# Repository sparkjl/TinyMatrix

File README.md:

## TinyMatrix点阵控制器
> 基于STM32F103 Microcontroller，HUB75接口的点阵控制器。可通过1 x 4按键、串口指令控制LED点阵屏显示。

### 1. 硬件
#### 1.1. HUB75接口定义
Led点阵板的HUB75接口，一般以DC3-16P牛角座封装形式接入。通常Led点阵板的左右两侧各有一个HUB75接口IN、OUT，以实现多块Led点阵板的组合扩展。HUB75接口中：R1、G1、B1分别为上半屏的红、绿、蓝控制信号，R2、G2、B2分别为下半屏的红、绿、蓝控制信号，A、B、C、D、E为行选择信号，CLK为数据时钟信号，LAT为数据锁存信号，OE为输出使能信号，GND为信号地。

<div align="center">
    
</div>

#### 1.2. HUB75扫描方式
将行扫描信号、行选择信号进行组合控制，就实现了整个Led点阵板的扫描显示。其具体实现过程如下：

<div align="center">
    
</div>

1. 从DATA_IN引脚（R1、G1、B1、R2、G2、B2）写入1 bit数据，将CLK引脚拉高产生上升沿将数据写入移位寄存器。如此循环m次将一行m bit数据传输至移位寄存器。
2. 将LATCH、<SPAN style="TEXT-DECORATION: overline">OE</SPAN>引脚拉高，m bit数据被从移位寄存器传输至缓存寄存器。同时缓存寄存器中数据被保持禁止从输出驱动器中输出，以使得在行选择信号切换时没有Led被点亮。
3. 切换并输出行选择信号。(初始状态时，第0行、第32行被选中。)
4. 将LATCH、<SPAN style="TEXT-DECORATION: overline">OE</SPAN>引脚拉低，m bit数据被从缓存寄存器传输至输出驱动器。同时移位寄存器中数据被锁存禁止从缓存寄存器中移出，此时对应选中行Led被点亮。

将以上步骤执行n/2次，便能实现m x n像素Led点阵板整个画面的扫描显示。如果扫描频率足够低，我们能看到逐行扫描显示的全过程：

<div align="center">
    
</div>

基于人眼视觉暂留效应（余晖效应），我们无法分辨刷新率在24Hz以上的动态画面。如果将扫描频率设置在60Hz，我们就能看到一幅完整的静态画面。而这也就是常见的显示器的基本原理。

最后，将Led点阵板上下两个部分的R1、G1、B1、R2、G2、B2控制信号进行组合，便能基于光学RGB模型实现全彩显示。

#### 1.3. Led Matrix控制板设计
了解了HUB75接口的控制原理，接下来进行Led Matrix控制板设计。

Led Matrix控制板设计思路如下：

<div align="center">
    
</div>

Led Matrix控制板的核心选择的是一款尺寸为 22.86mm x 53.34mm 的STM32最小系统板。其通过2 x 20Pin GPIO排针将板载STM32F103C8T6 MCU内集成的2x SPI、3x USART、2x I2C、1x CAN、37x I/O、2x ADC、4x Timer等硬件资源引出，以便外围扩展板调用。固件程序可通过SWD接口进行烧录和调试，可通过Reset键复位。板载2路Led灯，一路用于电源状态指示，一路用于程序状态指示。

<div align="center">
    
</div>

Led Matrix控制板设计1 x 4按键用于点阵控制器的参数设置。MCU相关GPIO经由74HC245连接至HUB75接口，以增加驱动电流并将驱动电压从3.3v转换至5.0v。外挂的W25Qxx系列SPI Flash用于存储系统参数和字库数据。UART串口可用于下载系统参数和字库数据，TTL-蓝牙模块、TTL-WiFi模块通过UART串口建立与MCU间的通讯以实现控制指令、显示数据的无线透传。Led Matrix控制板由外接电源适配器或内置锂离子电池提供系统电源，直流降压电路实现系统电源从12v-> 5v-> 3.3v电压转换以给各功能单元供电。

基于以上硬件需求，将Led Matrix控制板通过Eagle PCB设计如下。至于为什么是Eagle PCB，那是因为其小巧精悍、简单易用，丰富的元件库、精美的原理图、标准vector字体，无不透露着严谨精致。可惜的是，被Autodesk收购后的Eagle 9.6.2对于3D模型的预览编辑需要通过Fusion 360来实现。

<div align="center">
    
</div>
<div align="center">
    
</div>

### 2. 结构

Eagle 9.6.2不支持直接编辑3D封装，而只能通过Fusion 360以云托管元件库的方式导入。不想从Fusion 360中重构元件库，但又追求项目完整性，这怎么解决呢？那就选择KiCad，不仅支持3D封装的直接编辑，还能将Eagle的.sch原理图文件、.brd电路板文件转换成对应的KiCad格式文件。

使用KiCad将Led Matrix控制板的Eagle格式文件转换成KiCad格式文件，基于此添加编辑3D封装，导出Led Matrix控制板3D Step模型文件。

使用KiCad对MCU核心板重新进行layout，添加编辑3D封装，导出MCU核心板3D Step模型文件。

在Fusion 360中将Led Matrix控制板和MCU核心板进行零件装配、干涉检查。

在Fusion 360中将Led Matrix控制板设置为固定零件，以此为基准依据Led Matrix控制板的空间尺寸设计Led Matrix控制器的整体结构。选择亚克力板材作为外壳材质。顶部和底部亚克力板通过双通螺母柱进行连接，Led Matrix控制板和Led点阵板与底部亚克力板连接固定，四侧亚克力板与顶部和底部亚克力板通过卡扣扣合进行连接。

### 3. 软件
#### 3.1. RGB LED全彩显示
控制RGB LED实现全彩显示的传统方式是脉宽调制（Pulse Width Modulation），简称PWM。通过脉宽调制控制LED开关时间占比，进而实现RGB LED的亮度调节。如果对RGB模块中的三个LED进行此操作，则可以将红绿蓝三色按比例混合成对应的RGB全彩输出。对于Led Matrix Panel的全彩显示，PWM方式却不适用：这需要足够多的GPIO和定时器独立控制，需要消耗太多的硬件资源。那么我们如何通过软件方式予以解决呢？  

二进制编码调制（Binary Code Modulation），简称BCM。BCM利用二进制编码性质控制开关信号占空比。假设有一个位宽为4的二进制数：从其最低位向左移动至最高位依次表示1个时间切片、2个时间切片、4个时间切片、8个时间切片。将这4种时间切片混合，可产生分辨率为1/15的任意占空比。如此，位宽越大分辨率越高色彩越丰富。位宽为8的二进制数，可表示分辨率为1/255的任意占空比。但位宽越大，时间切片越小，意味着更高的CPU占用率。为更好地平衡系统性能和硬件资源，本项目中BCM位宽为4。例如，4位二进制数0101表示5/15或33.3%的占空比。

<div align="center">
    
</div>

Led Matrix Panel是逐行扫描显示的，所以需要预先将图像像素色彩转换成BCM值保存至图像缓冲区。创建4个图像缓冲区，以表示BCM位宽为4情况下的4种长度的时间切片中在扫描时间范围内哪些时间切片需要点亮LED。将这4个图像缓冲区构成的4个颜色通道Plane，进行图像融合就构成了一幅完整的静态图像。

<div align="center">
    
</div>

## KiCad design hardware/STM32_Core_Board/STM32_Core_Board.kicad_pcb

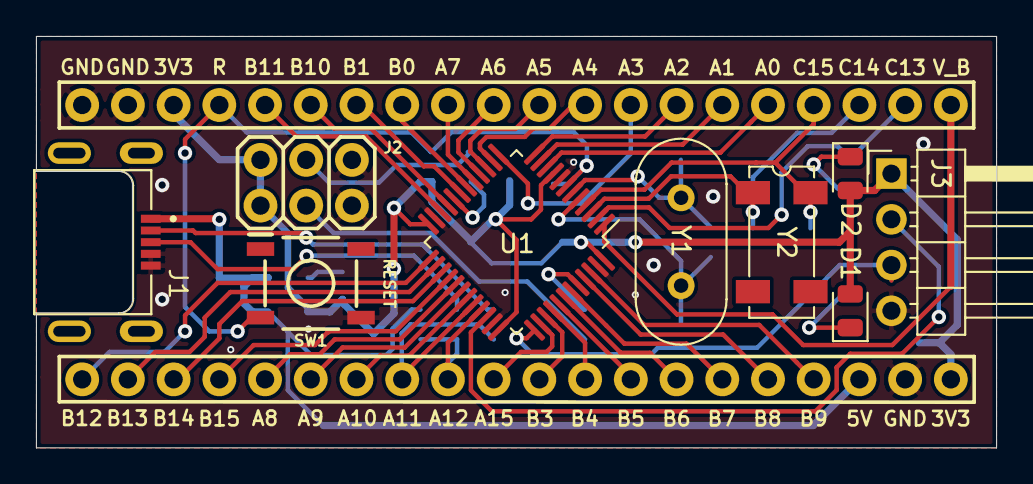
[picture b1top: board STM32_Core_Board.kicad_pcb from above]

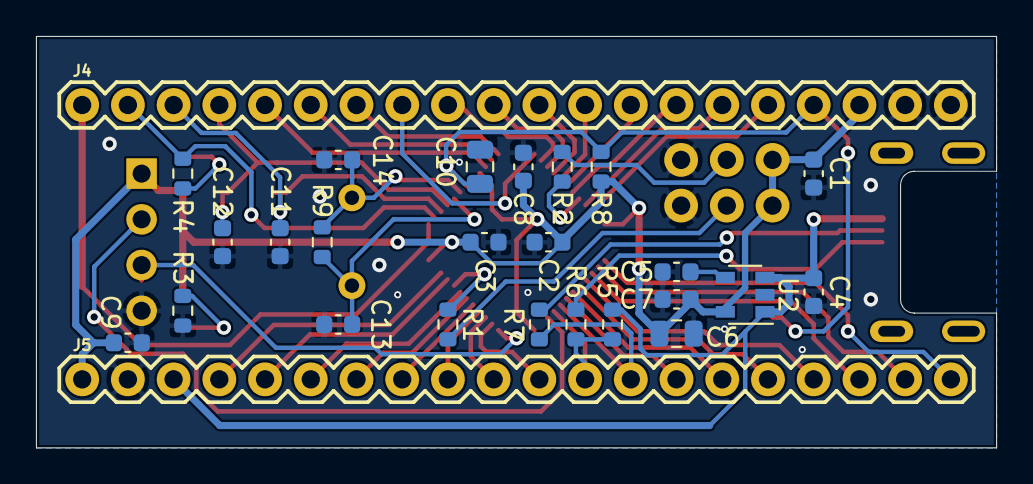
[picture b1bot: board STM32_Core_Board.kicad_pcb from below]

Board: 2 copper layers, 53.3 x 22.9 mm, 35 parts (26 on the bottom side), 50 nets.

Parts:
C1, C2, C3, C7, C8, C9: 104; C_0603_1608Metric
C4: 105; C_0603_1608Metric
C5: 223; C_0603_1608Metric
C6: 106; C_0805_2012Metric
C10: 105; C_0805_2012Metric
C11, C12, C13, C14: 20pF; C_0603_1608Metric
D1, D2: LED; LED_0805_2012Metric
J1: USB_B_Micro; USB_Micro-B-MOLEX_47642-0001
J2: Header 3x2; 2X3
J3: SWD; PinHeader_1x04_P2.54mm_Horizontal
J4, J5: Conn_01x20_Male; 1X20
R1, R2: 100K; R_0603_1608Metric
R3, R4: 510R; R_0603_1608Metric
R5: 4.7K; R_0603_1608Metric
R6, R7: 20R; R_0603_1608Metric
R8: 10K; R_0603_1608Metric
R9: 1M; R_0603_1608Metric
SW1: RESET; TACTILE_SWITCH_SMD_5.2MM
U1: STM32F103C8Tx; LQFP-48_7x7mm_P0.5mm
U2: SPX3819M5-L-3-3; SOT-23-5
Y1: 8MHz; Crystal_HC49-4H_Vertical
Y2: Crystal_GND23_Small; Crystal_SMD_SeikoEpson_MC306-4Pin_8.0x3.2mm

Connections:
+3V3: C1.1, C2.1, C3.1, C6.1, C7.1, C8.1, C9.1, D1.2, D2.2, J2.1, J2.2, J3.1, J4.18, J5.1, R8.1, U1.9, U1.24, U1.36, U1.48, U2.5
+5V: C4.1, J1.1, J5.3, R5.2, U2.1, U2.3
/BOOT0: R1.1, U1.44
/BOOT1: R2.2, U1.20
/OSCIN: C13.1, R9.1, U1.5, Y1.1
/OSCOUT: C14.1, R9.2, U1.6, Y1.2
/PA0: J4.5, U1.10
/PA1: J4.6, U1.11
/PA2: J4.7, U1.12
/PA3: J4.8, U1.13
/PA4: J4.9, U1.14
/PA5: J4.10, U1.15
/PA6: J4.11, U1.16
/PA7: J4.12, U1.17
/PA8: J5.16, U1.29
/PA9: J5.15, U1.30
/PA10: J5.14, U1.31
/PA11: J5.13, R7.1, U1.32
/PA12: J5.12, R5.1, R6.1, U1.33
/PA13: J3.2, U1.34
/PA14: J3.3, U1.37
/PA15: J5.11, U1.38
/PB0: J4.13, U1.18
/PB1: J4.14, U1.19
/PB3: J5.10, U1.39
/PB4: J5.9, U1.40
/PB5: J5.8, U1.41
/PB6: J5.7, U1.42
/PB7: J5.6, U1.43
/PB8: J5.5, U1.45
/PB9: J5.4, U1.46
/PB10: J4.15, U1.21
/PB11: J4.16, U1.22
/PB12: J5.20, U1.25
/PB13: J5.19, U1.26
/PB14: J5.18, U1.27
/PB15: J5.17, U1.28
/PC13: J4.2, R4.1, U1.2
/PC14: C11.1, J4.3, U1.3, Y2.1
/PC15: C12.1, J4.4, U1.4, Y2.4
/RESET: C10.1, J4.17, R8.2, SW1.2, U1.7
GND: C1.2, C2.2, C3.2, C4.2, C5.2, C6.2, C7.2, C8.2, C9.2, C10.2, C11.2, C12.2, C13.2, C14.2, J1.4, J1.5, J2.5, J2.6, J3.4, J4.19, J4.20, J5.2, R3.1, SW1.1, U1.8, U1.23, U1.35, U1.47, U2.2
unnamed: C5.1, U2.4
unnamed: D1.1, R3.2
unnamed: D2.1, R4.2
unnamed: J1.2, R7.2
unnamed: J1.3, R6.2
unnamed: J2.3, R1.2
unnamed: J2.4, R2.1
V_BATT: J4.1, U1.1

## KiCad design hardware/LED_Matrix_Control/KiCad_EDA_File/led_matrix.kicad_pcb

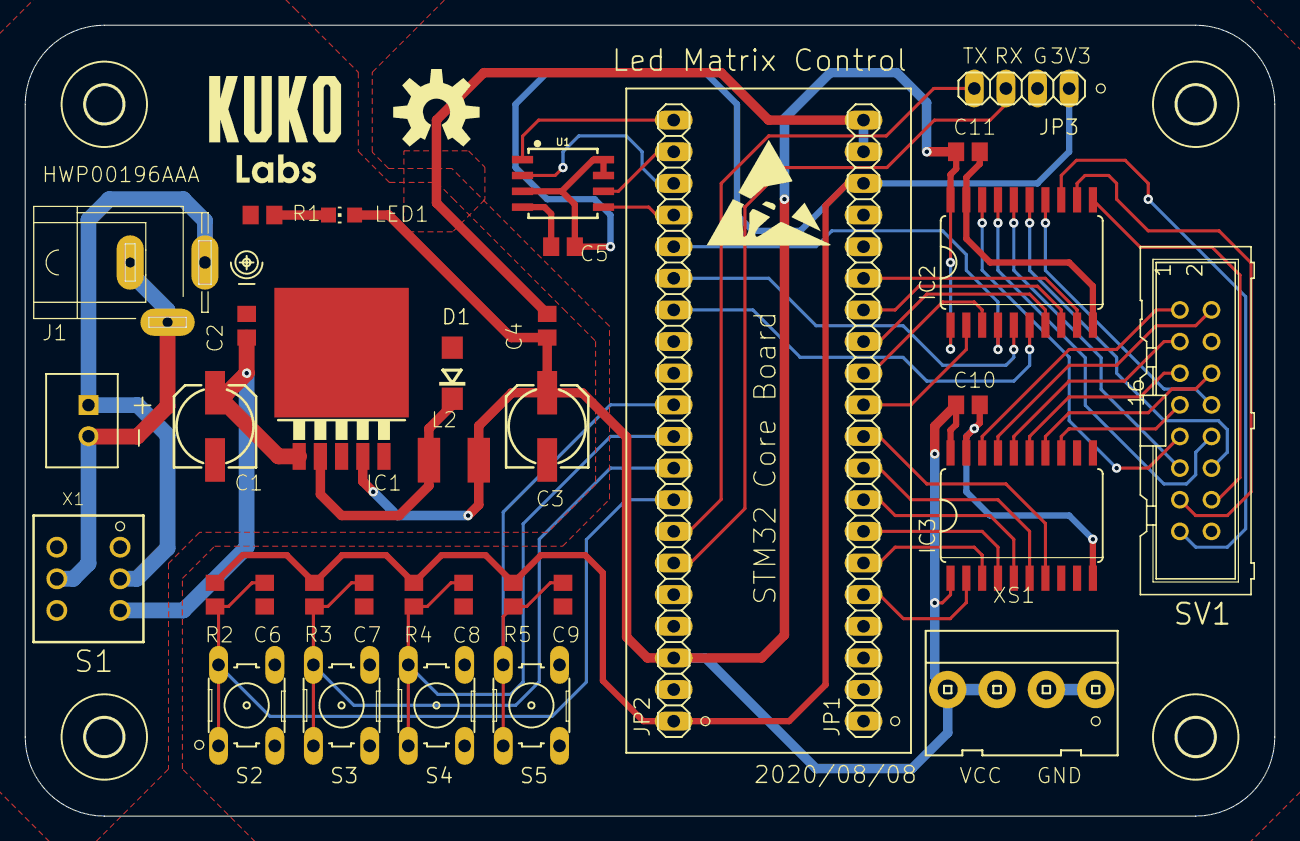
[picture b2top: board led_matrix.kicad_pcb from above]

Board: 2 copper layers, 100.3 x 63.5 mm, 42 parts (0 on the bottom side), 46 nets.

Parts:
C1, C3: 220uF; 153CLV-0605
C2, C4, C5, C6, C7, C8, C9, C10, C11: 104; C0805
D1: SS34; DO214AC
IC1: LM2596S; TO263-5
IC2, IC3: 74245DW; SO20W
J1: JACK-PLUG0; SPC4077
JP1, JP2: PINHD-1X20; 1X20
JP3: PINHD-1X4; 1X04
L2: L-USL4532P; L4532P
LED1: LEDCHIP-LED0805; CHIP-LED0805
R1: 10K; R0805
R2, R3, R4, R5: 47K; R0805
S1: TL46PO; TL4XPO
S2, S3, S4, S5: 10-XX; B3F-10XX
SV1: ML16
U1: W25Q32FV; SOIC-8
U$1: LOGO?; LOGO
U$2, U$3, U$4, U$5: 3,0
U$6: ESD_10.00
U$7: OSHW-LOGO-L
X1: B2B-XH-A
XS1: C4; NINIGI4C

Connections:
+3V3: C5.1, JP1.18, JP2.1, JP3.1, R2.1, R3.1, R4.1, R5.1, U1.3, U1.7, U1.8
+5V: C3.+, C4.1, C10.1, C11.1, IC1.4, IC2.1, IC2.20, IC3.1, IC3.20, JP2.3, L2.2, LED1.A, XS1.3, XS1.4
/A: IC2.18, SV1.9
/B: IC2.17, SV1.10
/C: IC2.16, SV1.11
/CLK: IC2.12, SV1.13
/D: IC2.15, SV1.12
/DB1: IC3.16, SV1.3
/DB2: IC3.13, SV1.7
/DG1: IC3.17, SV1.2
/DG2: IC3.14, SV1.6
/DR1: IC3.18, SV1.1
/DR2: IC3.15, SV1.5
/E: IC2.14, SV1.8
/KEY1: C6.1, JP2.8, R2.2, S2.1, S2.2
/KEY2: C7.1, JP2.9, R3.2, S3.1, S3.2
/KEY3: C8.1, JP2.10, R4.2, S4.1, S4.2
/KEY4: C9.1, JP2.11, R5.2, S5.1, S5.2
/LAT: IC2.11, SV1.14
/OE: IC2.13, SV1.15
/SPI2_CS: JP2.20, U1.1
/SPI2_MISO: JP2.18, U1.2
/SPI2_MOSI: JP2.17, U1.5
/SPI2_SCK: JP2.19, U1.6
/UART1_RX: JP2.6, JP3.3
/UART1_TX: JP2.7, JP3.4
/_A: IC2.2, JP1.11
/_B: IC2.3, JP1.12
/_C: IC2.4, JP2.16
/_CLK: IC2.8, JP1.14
/_D: IC2.5, JP2.15
/_DB1: IC3.4, JP1.7
/_DB2: IC3.7, JP1.10
/_DG1: IC3.3, JP1.6
/_DG2: IC3.6, JP1.9
/_DR1: IC3.2, JP1.5
/_DR2: IC3.5, JP1.8
/_E: IC2.6, JP2.14
/_LAT: IC2.9, JP1.15
/_OE: IC2.7, JP1.13
GND: C1.-, C2.2, C3.-, C4.2, C5.2, C6.2, C7.2, C8.2, C9.2, C10.2, C11.2, D1.A, IC1.3, IC1.5, IC2.10, IC2.19, IC3.10, IC3.19, JP1.19, JP1.20, JP2.2, JP3.2, R1.1, S1.6, S2.3, S2.4, S3.3, S3.4, S4.3, S4.4, S5.3, S5.4, SV1.4, SV1.16, U1.4, XS1.1, XS1.2
unnamed: C1.+, C2.1, IC1.1, S1.3
unnamed: D1.C, IC1.2, L2.1
unnamed: J1.1, J1.2, S1.5, X1.2
unnamed: J1.3, S1.2, X1.1
unnamed: LED1.C, R1.2

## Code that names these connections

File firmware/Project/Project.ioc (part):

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Mcu.Name=STM32F103C(8-B)Tx
Mcu.Package=LQFP48
Mcu.UserName=STM32F103C8Tx
PA0-WKUP.GPIOParameters=GPIO_Label
PA0-WKUP.GPIO_Label=HUB75_DR1
PA0-WKUP.Signal=GPIO_Output
PA1.GPIOParameters=GPIO_Label
PA1.GPIO_Label=HUB75_DG1
PA1.Signal=GPIO_Output
PA10.GPIOParameters=GPIO_Label
PA10.GPIO_Label=HUB75_E
PA10.Signal=GPIO_Output
PA11.Mode=Device
PA11.Signal=USB_DM
PA12.Mode=Device
PA12.Signal=USB_DP
PA13.Mode=Serial_Wire
PA13.Signal=SYS_JTMS-SWDIO
PA14.Mode=Serial_Wire
PA14.Signal=SYS_JTCK-SWCLK
PA15.GPIOParameters=GPIO_Label
PA15.GPIO_Label=KEY_4
PA15.Signal=GPIO_Input
PA2.GPIOParameters=GPIO_Label
PA2.GPIO_Label=HUB75_DB1
PA2.Signal=GPIO_Output
PA3.GPIOParameters=GPIO_Label
PA3.GPIO_Label=HUB75_DR2
PA3.Signal=GPIO_Output
PA4.GPIOParameters=GPIO_Label
PA4.GPIO_Label=HUB75_DG2
PA4.Signal=GPIO_Output
PA5.GPIOParameters=GPIO_Label
PA5.GPIO_Label=HUB75_DB2
PA5.Signal=GPIO_Output
PA6.GPIOParameters=GPIO_Label
PA6.GPIO_Label=HUB75_A
PA6.Signal=GPIO_Output
PA7.GPIOParameters=GPIO_Label
PA7.GPIO_Label=HUB75_B
PA7.Signal=GPIO_Output
PA8.GPIOParameters=GPIO_Label
PA8.GPIO_Label=HUB75_C
PA8.Signal=GPIO_Output
PA9.GPIOParameters=GPIO_Label
PA9.GPIO_Label=HUB75_D
PA9.Signal=GPIO_Output
PB0.GPIOParameters=GPIO_Label
PB0.GPIO_Label=HUB75_OE
PB0.Signal=GPIO_Output
PB1.GPIOParameters=GPIO_Label
PB1.GPIO_Label=HUB75_CLK
PB1.Signal=GPIO_Output
PB10.GPIOParameters=GPIO_Label
PB10.GPIO_Label=HUB75_LAT
PB10.Signal=GPIO_Output
PB12.GPIOParameters=GPIO_Speed,PinState,GPIO_Label
PB12.GPIO_Label=SPI2_CS
PB12.GPIO_Speed=GPIO_SPEED_FREQ_HIGH
PB12.PinState=GPIO_PIN_SET
PB12.Signal=GPIO_Output
PB13.Mode=Full_Duplex_Master
PB13.Signal=SPI2_SCK
PB14.Mode=Full_Duplex_Master
PB14.Signal=SPI2_MISO
PB15.Mode=Full_Duplex_Master
PB15.Signal=SPI2_MOSI
PB3.GPIOParameters=GPIO_Label
PB3.GPIO_Label=KEY_3
PB3.Signal=GPIO_Input
PB4.GPIOParameters=GPIO_Label
PB4.GPIO_Label=KEY_2
PB4.Signal=GPIO_Input
PB5.GPIOParameters=GPIO_Label
PB5.GPIO_Label=KEY_1
PB5.Signal=GPIO_Input
PB6.Mode=Asynchronous
PB6.Signal=USART1_TX
PB7.Mode=Asynchronous
PB7.Signal=USART1_RX
PC13-TAMPER-RTC.GPIOParameters=GPIO_Label
PC13-TAMPER-RTC.GPIO_Label=LED1
PC13-TAMPER-RTC.Signal=GPIO_Output
PC14-OSC32_IN.Mode=LSE-External-Oscillator
PC14-OSC32_IN.Signal=RCC_OSC32_IN
PC15-OSC32_OUT.Mode=LSE-External-Oscillator
PC15-OSC32_OUT.Signal=RCC_OSC32_OUT
PD0-OSC_IN.Mode=HSE-External-Oscillator
PD0-OSC_IN.Signal=RCC_OSC_IN
PD1-OSC_OUT.Mode=HSE-External-Oscillator
PD1-OSC_OUT.Signal=RCC_OSC_OUT
RCC.SYSCLKFreq_VALUE=72000000
RCC.SYSCLKSource=RCC_SYSCLKSOURCE_PLLCLK
board=custom

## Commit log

2021-06-06 draft commit
2021-06-14 hub75 timing control via Timer TIM2
2021-06-20 long press KEY_ENTER to setup sys data
2021-06-20 change Menu MODE to Menu FONT: select&display, upgrade, erase font data
2021-07-11 add uart link protocol, modify crc16 check algorithm.
2021-07-18 uart link: restart uart rx before restart uart tx
2021-07-29 sort out
2021-07-31 font display upgrade
2021-08-02 add Freq Menu to set up display frequency and shift period
2021-08-14 Create images
2021-08-14 add image files
2021-08-14 revise README.md
2021-08-23 draft commit: driver for ICN2053
2021-08-29 driver for ICN2053/ICN2153
2021-08-31 adjust color channel
2021-09-04 disable OE output after initializing
2022-10-11 1.upgrade the firmware package to STM32Cube_FW_F1_V1.8.4 2.enlarge the capacity of heap and stack
